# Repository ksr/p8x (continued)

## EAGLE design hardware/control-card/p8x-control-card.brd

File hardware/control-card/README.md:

# Control / Microcode Card

> **Theory of operation:** [p8x-control-card-theory.md](p8x-control-card-theory.md) — deep walkthrough of inputs/outputs, signal flow, and logic.

The brain of the P8X. It generates the clock, handles reset and the front-panel
run controls, holds the instruction register, and — most importantly — runs the
**microcode engine** that drives every other card over the backplane. If a signal
on the bus tells another card what to do (DOE, DLD, PSEL, ALU function, …), it
originated here.

> This README describes the circuit as actually built in
> [`generators/gen_eagle.py`](../../generators/gen_eagle.py) (the canonical
> source). For the architectural overview see
> [p8x-system-design.md §3](../../docs/p8x-system-design.md); for bus pin assignments see
> [p8x-bus-definition.md](../backplane/p8x-bus-definition.md).

## Chip inventory

| Ref | Device | Role |
|-----|--------|------|
| U1 | 74161 | Clock divider (÷2 and ÷4 taps for JP1) |
| U2 | 74HCT14 | Schmitt inverters — reset & switch debounce |
| U3 | 7474 | Dual D flip-flop — run/step synchronizer |
| U4 | 74HCT00 | NAND glue |
| U5 | 74HCT08 | AND glue (clock gating) |
| U6 | 74HCT32 | OR glue |
| U7 | 74377 | Instruction register (8-bit, load-enabled) |
| U8 | 74138 | DLD decoder → generates the IR-load strobe |
| U9 | 74151 | Condition multiplexer (selects 1 of 8 condition sources) |
| U10–U13 | 28C64 | Microcode ROM, 4 × 8 bits = the 32-bit control word |
| U14–U17 | 74374 | Pipeline register (latches the control word on CLK̄) |
| U18 | 74161 | Microcode step counter |
| X1 | 4 MHz osc | Master clock source |

## How it works

### Clock generation
The 4 MHz oscillator (X1) feeds the 74161 divider (U1). Jumper **JP1** (a 2x3
header) selects the raw oscillator or a ÷2/÷4 tap, so you can slow the machine down
for debugging: one shunt on pins 1-2 = 4 MHz, 3-4 = 2 MHz, 5-6 = 1 MHz.
The selected clock is gated (U5/U6) by the run/halt logic and then split into
**CLK** and its inverse **CLK̄** (via U2), both broadcast on the backplane. CLK
clocks the working registers; CLK̄ clocks the pipeline latch a half-cycle earlier
so the control word is already stable when CLK arrives.

### Reset
A pushbutton + RC network feeds two 74HCT14 Schmitt inverters (U2) to produce a
clean, debounced **-RES**. Reset clears the step counter (U18) and the instruction
register (U7), and is broadcast on the backplane so every card returns to a known
state (notably the Register Bank zeroes P0 → execution starts at $0000).

### Front-panel run control
- **RUN/HALT** toggle and a debounced **STEP** pushbutton feed a 7474 (U3)
  synchronizer. Clocking the request through a flip-flop guarantees the machine
  always stops on a **microcycle boundary**, never mid-cycle.
- The microcode **HALT** bit ORs into the same stop logic (U6), so software can
  halt the clock; only the front panel can restart it.

### The microcode engine — the core loop
1. The **instruction register** (U7, a 74377) holds the current opcode. It loads
   from the data bus when the DLD field = 6, decoded by U8 (74138) into the
   `-IRLD` strobe.
2. The microcode ROM address is assembled as **`IR | step<<8 | cond<<12`**:
   - opcode (8 bits) from U7,
   - step number (4 bits) from the U18 step counter,
   - one selected **condition** bit from U9 (74151), chosen by the FCOND field.
3. Four **28C64 EPROMs** (U10–U13) output the 32-bit control word at that address.
4. The 4 × **74374** pipeline latch (U14–U17) registers all 32 bits on CLK̄, so
   glitchy ROM transitions never reach the backplane. The latched outputs *are*
   the bus control signals: DOE0–3, DLD0–3, PSEL0–1, PINC, PDEC, ALUS0–3, ALUM,
   CIN, SH0–1, LDF, FCOND0–2, plus µRESET and HALT.
5. The step counter (U18) increments each cycle. The **µRESET** bit reloads it to
   zero, ending the current instruction and forcing the shared fetch cycle next.

### Condition multiplexer
U9 (74151) selects one of the flag/condition inputs (FC, FZ, FN, FV, hard 0/1, …)
based on the FCOND field, and feeds it into ROM address bit 12. This is how a
single opcode can branch to two different microcode paths (taken vs not-taken)
without any extra sequencing logic — the condition literally selects a different
ROM page.

## Control word layout (32 bits)
See [p8x-system-design.md §3.2](../../docs/p8x-system-design.md) for the full bit map, and
`microcode/genucode.py` `w()` for the authoritative packing. In brief: bits 0–3
DOE, 4–7 DLD, 8–10 PSEL (3-bit: P0–P3 + PT scratch), 11 PINC, 12 PDEC, 13–16 ALU
S0–3, 17 ALU M, 18 CIN, 19–20 SH0/1, 21 LDF, 22–24 FCOND, 25 µRESET, 26 HALT,
27 LDZN, 28 SHCIN, 29 SETC, 30 CLRC, 31 BSEL.

## LEDs
PWR (green), RUN (green), HALT (red) — driven from the run/halt state.

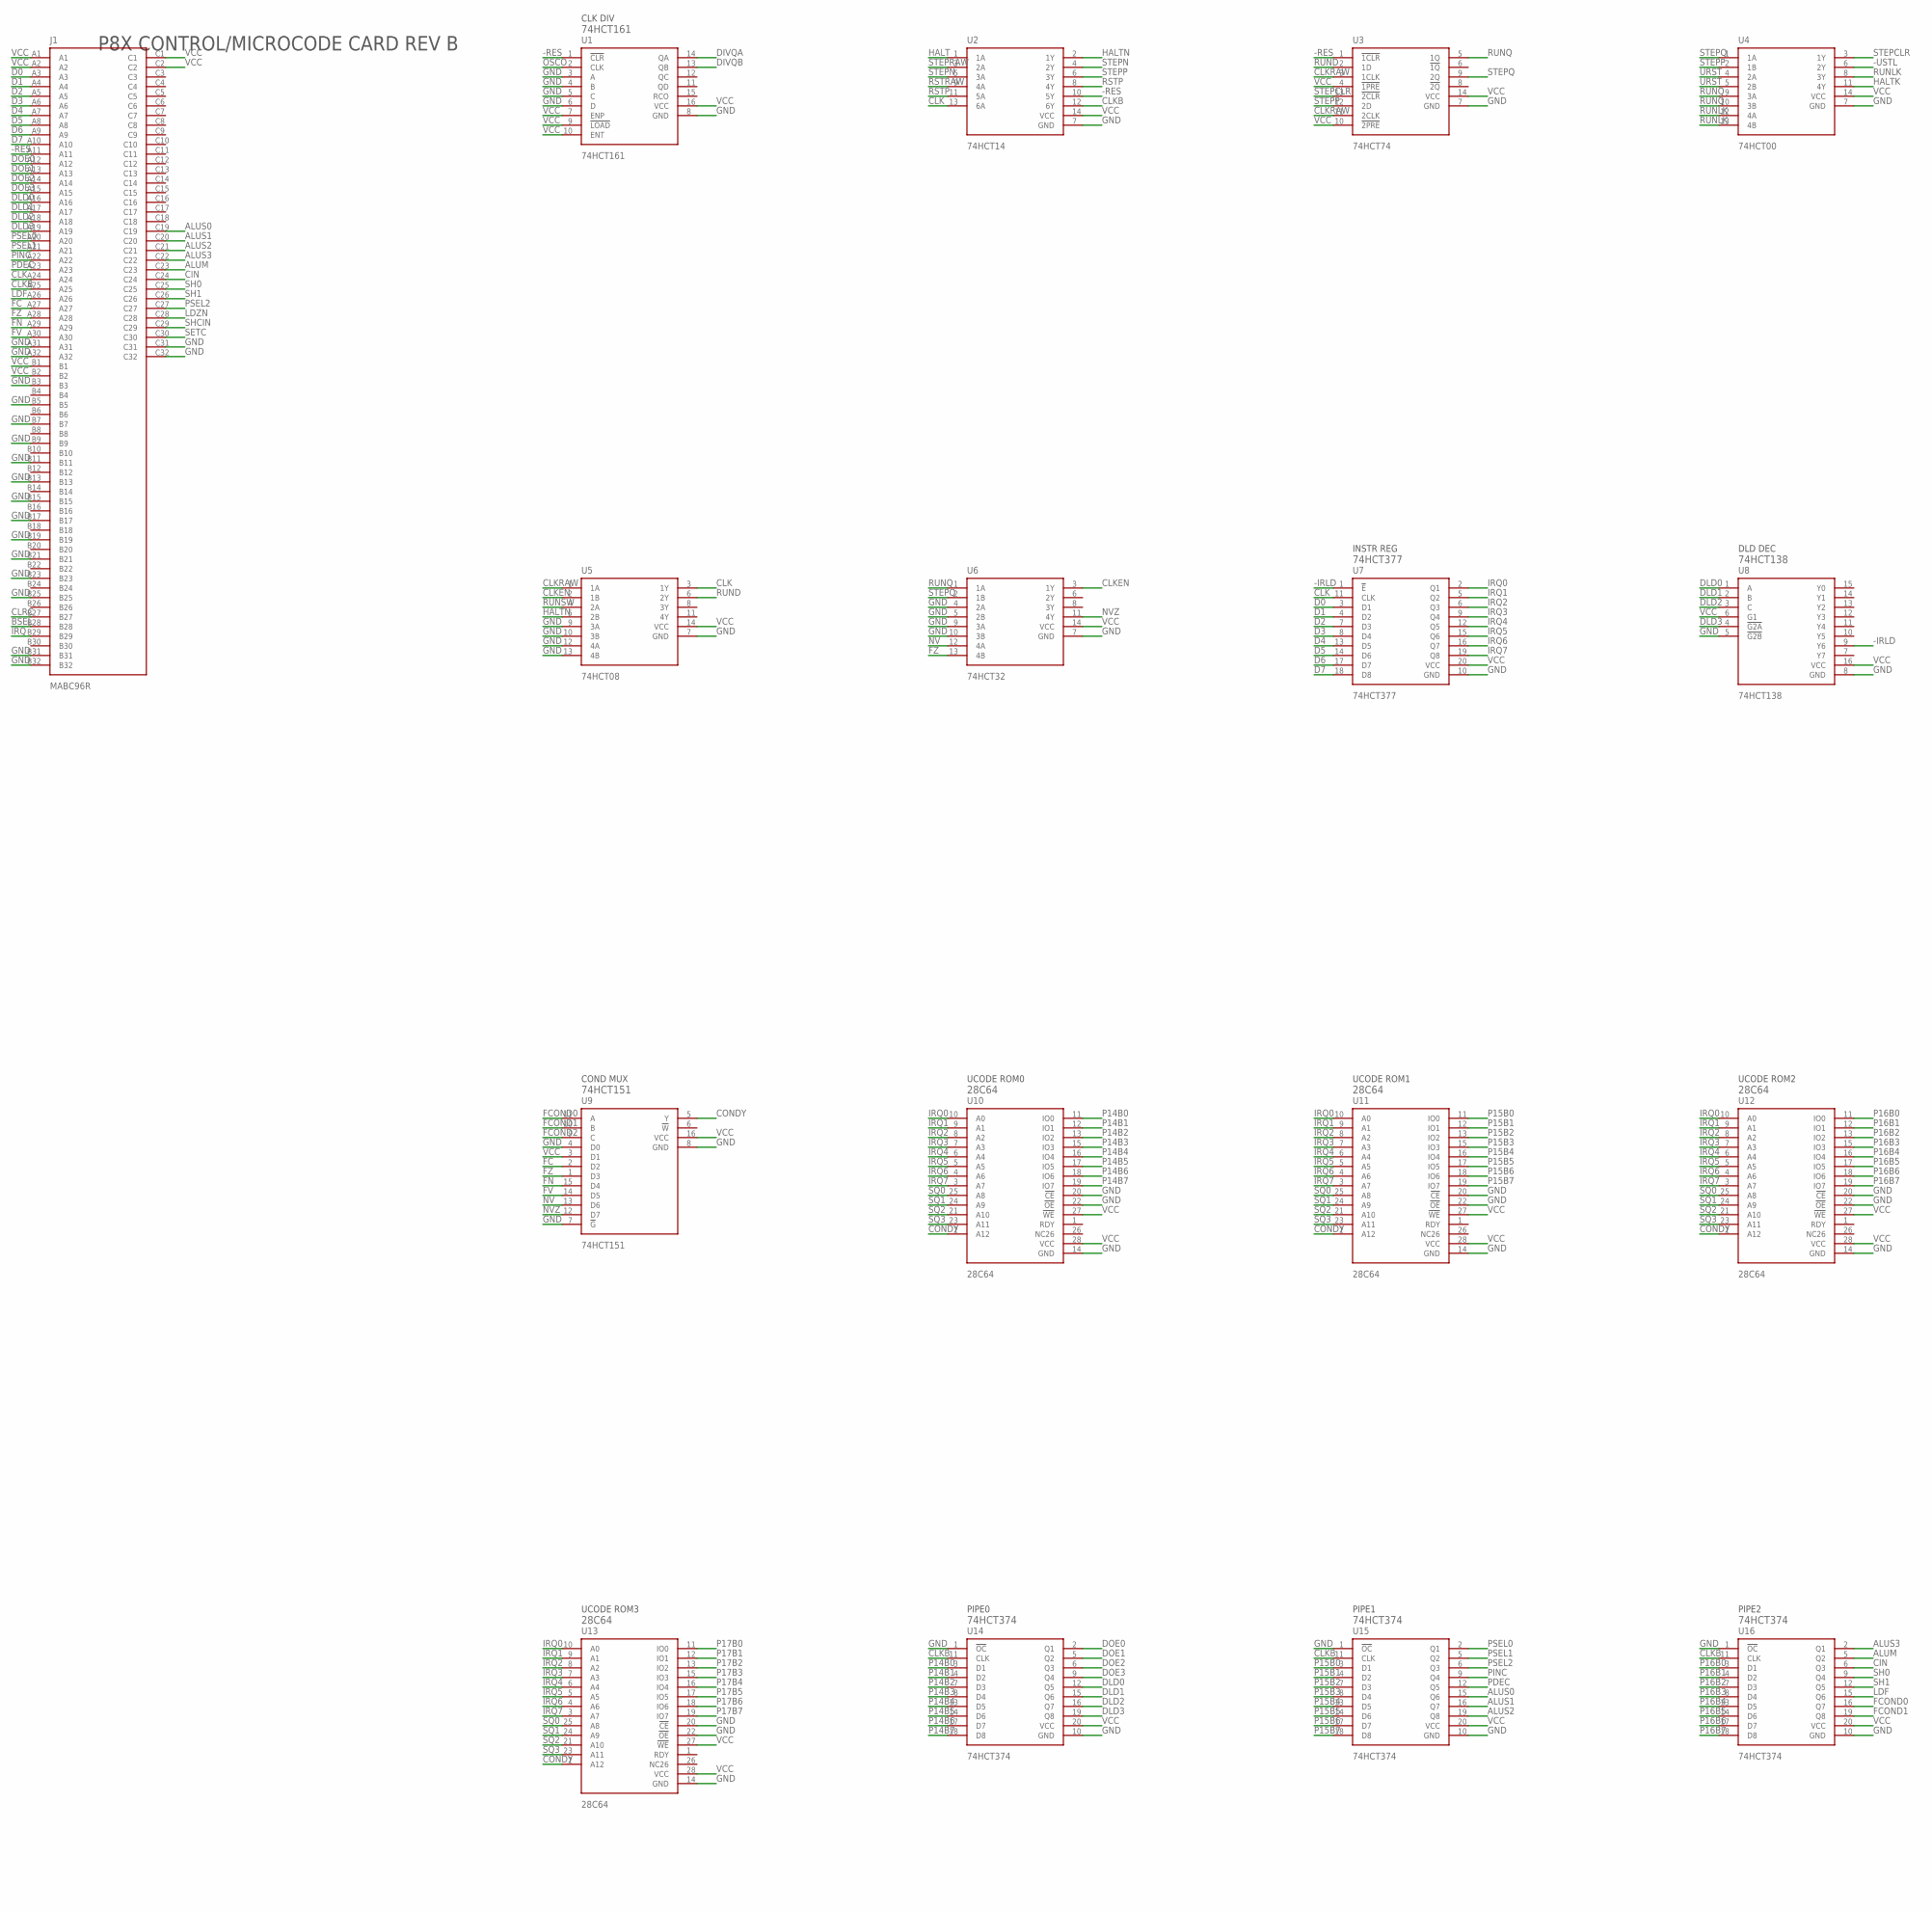
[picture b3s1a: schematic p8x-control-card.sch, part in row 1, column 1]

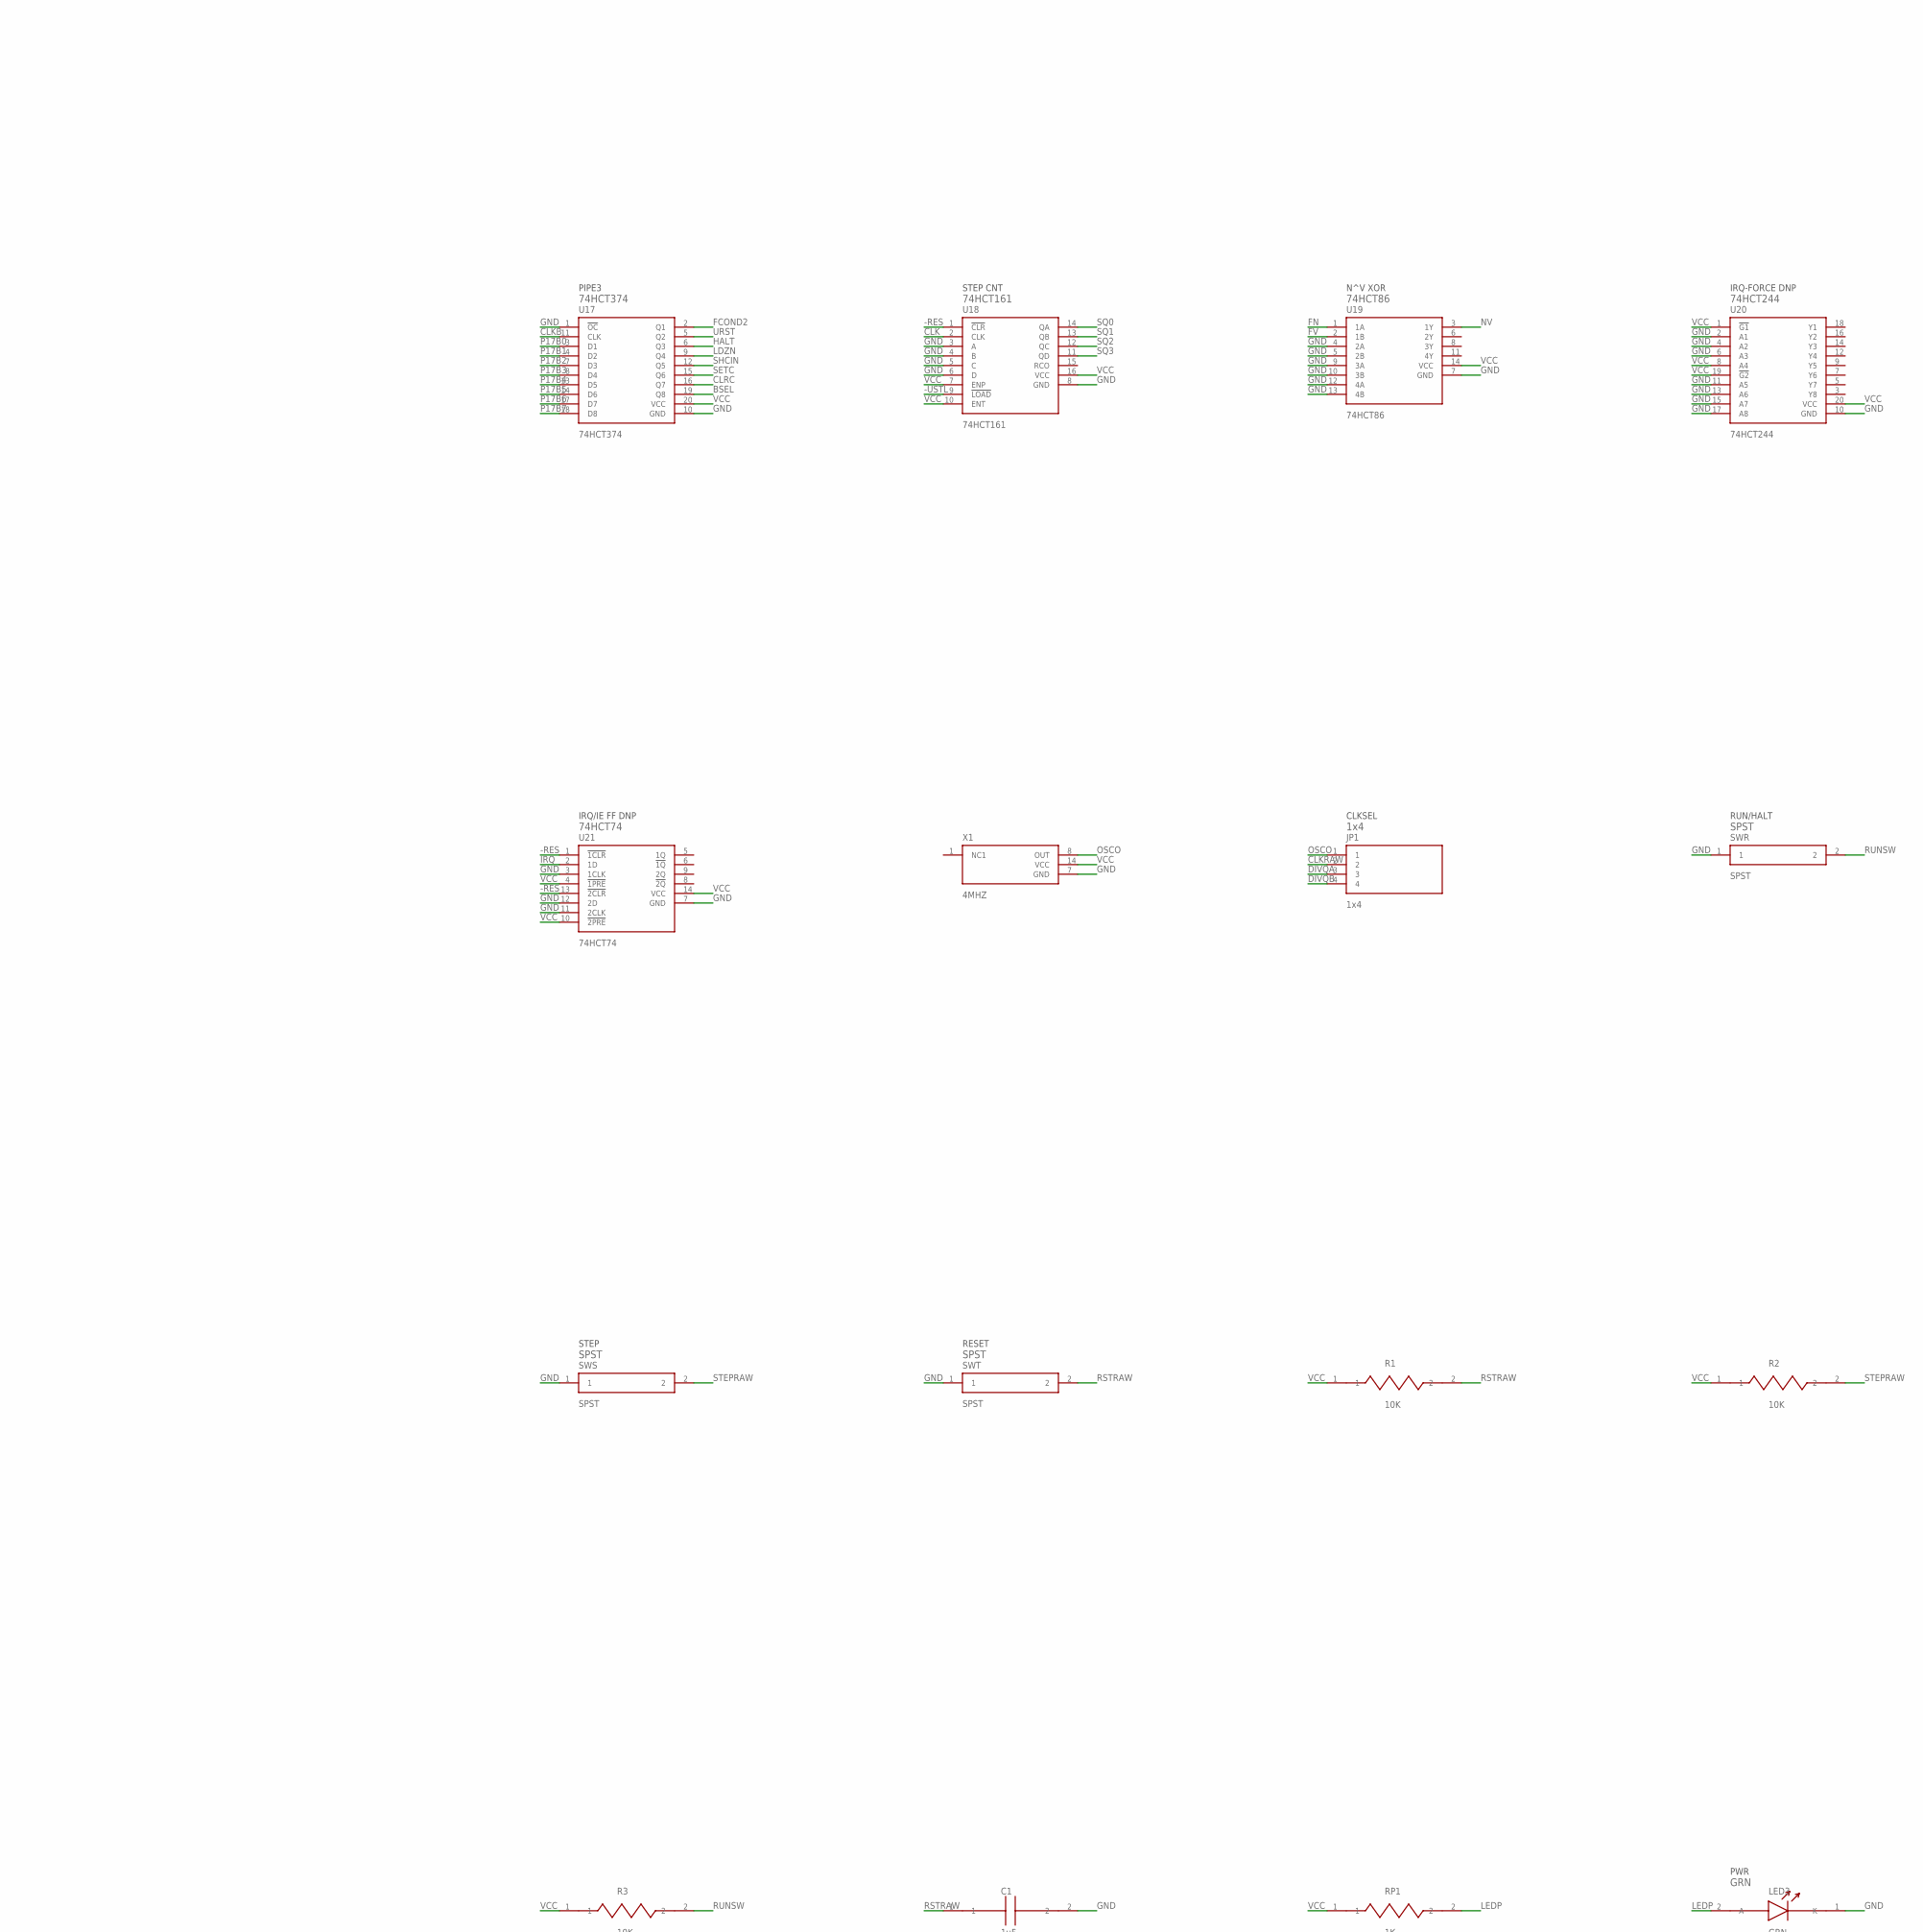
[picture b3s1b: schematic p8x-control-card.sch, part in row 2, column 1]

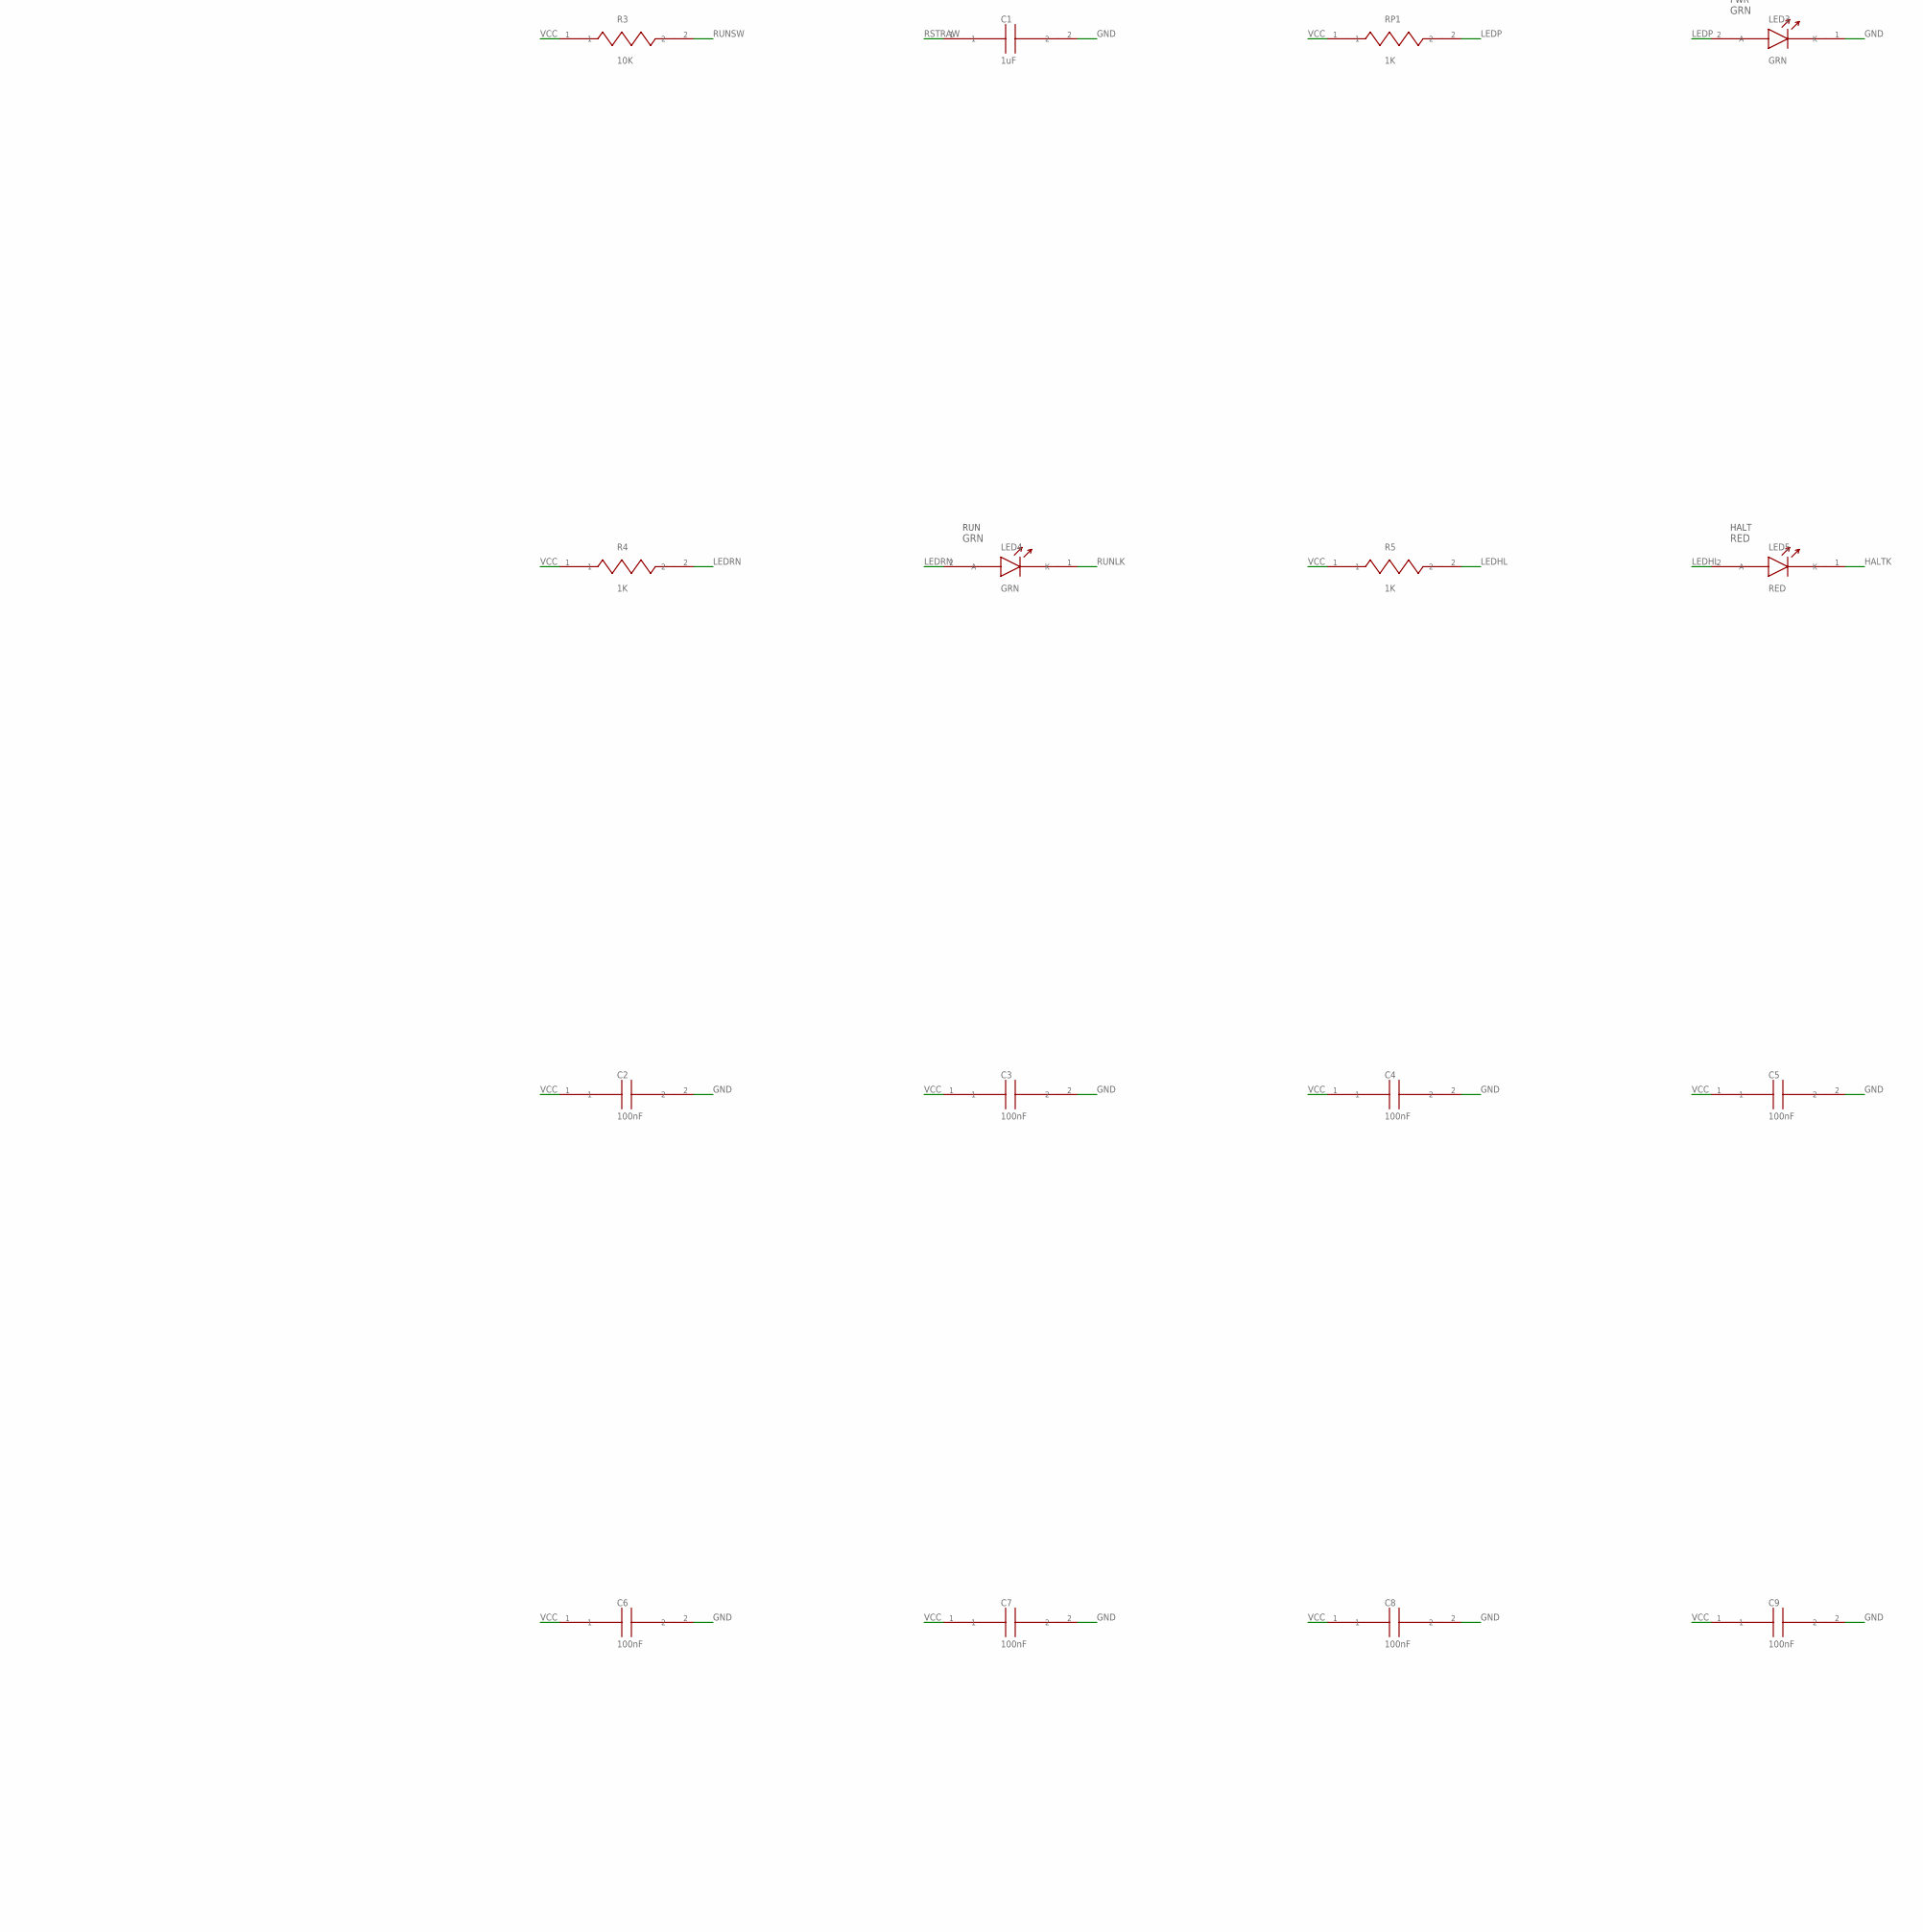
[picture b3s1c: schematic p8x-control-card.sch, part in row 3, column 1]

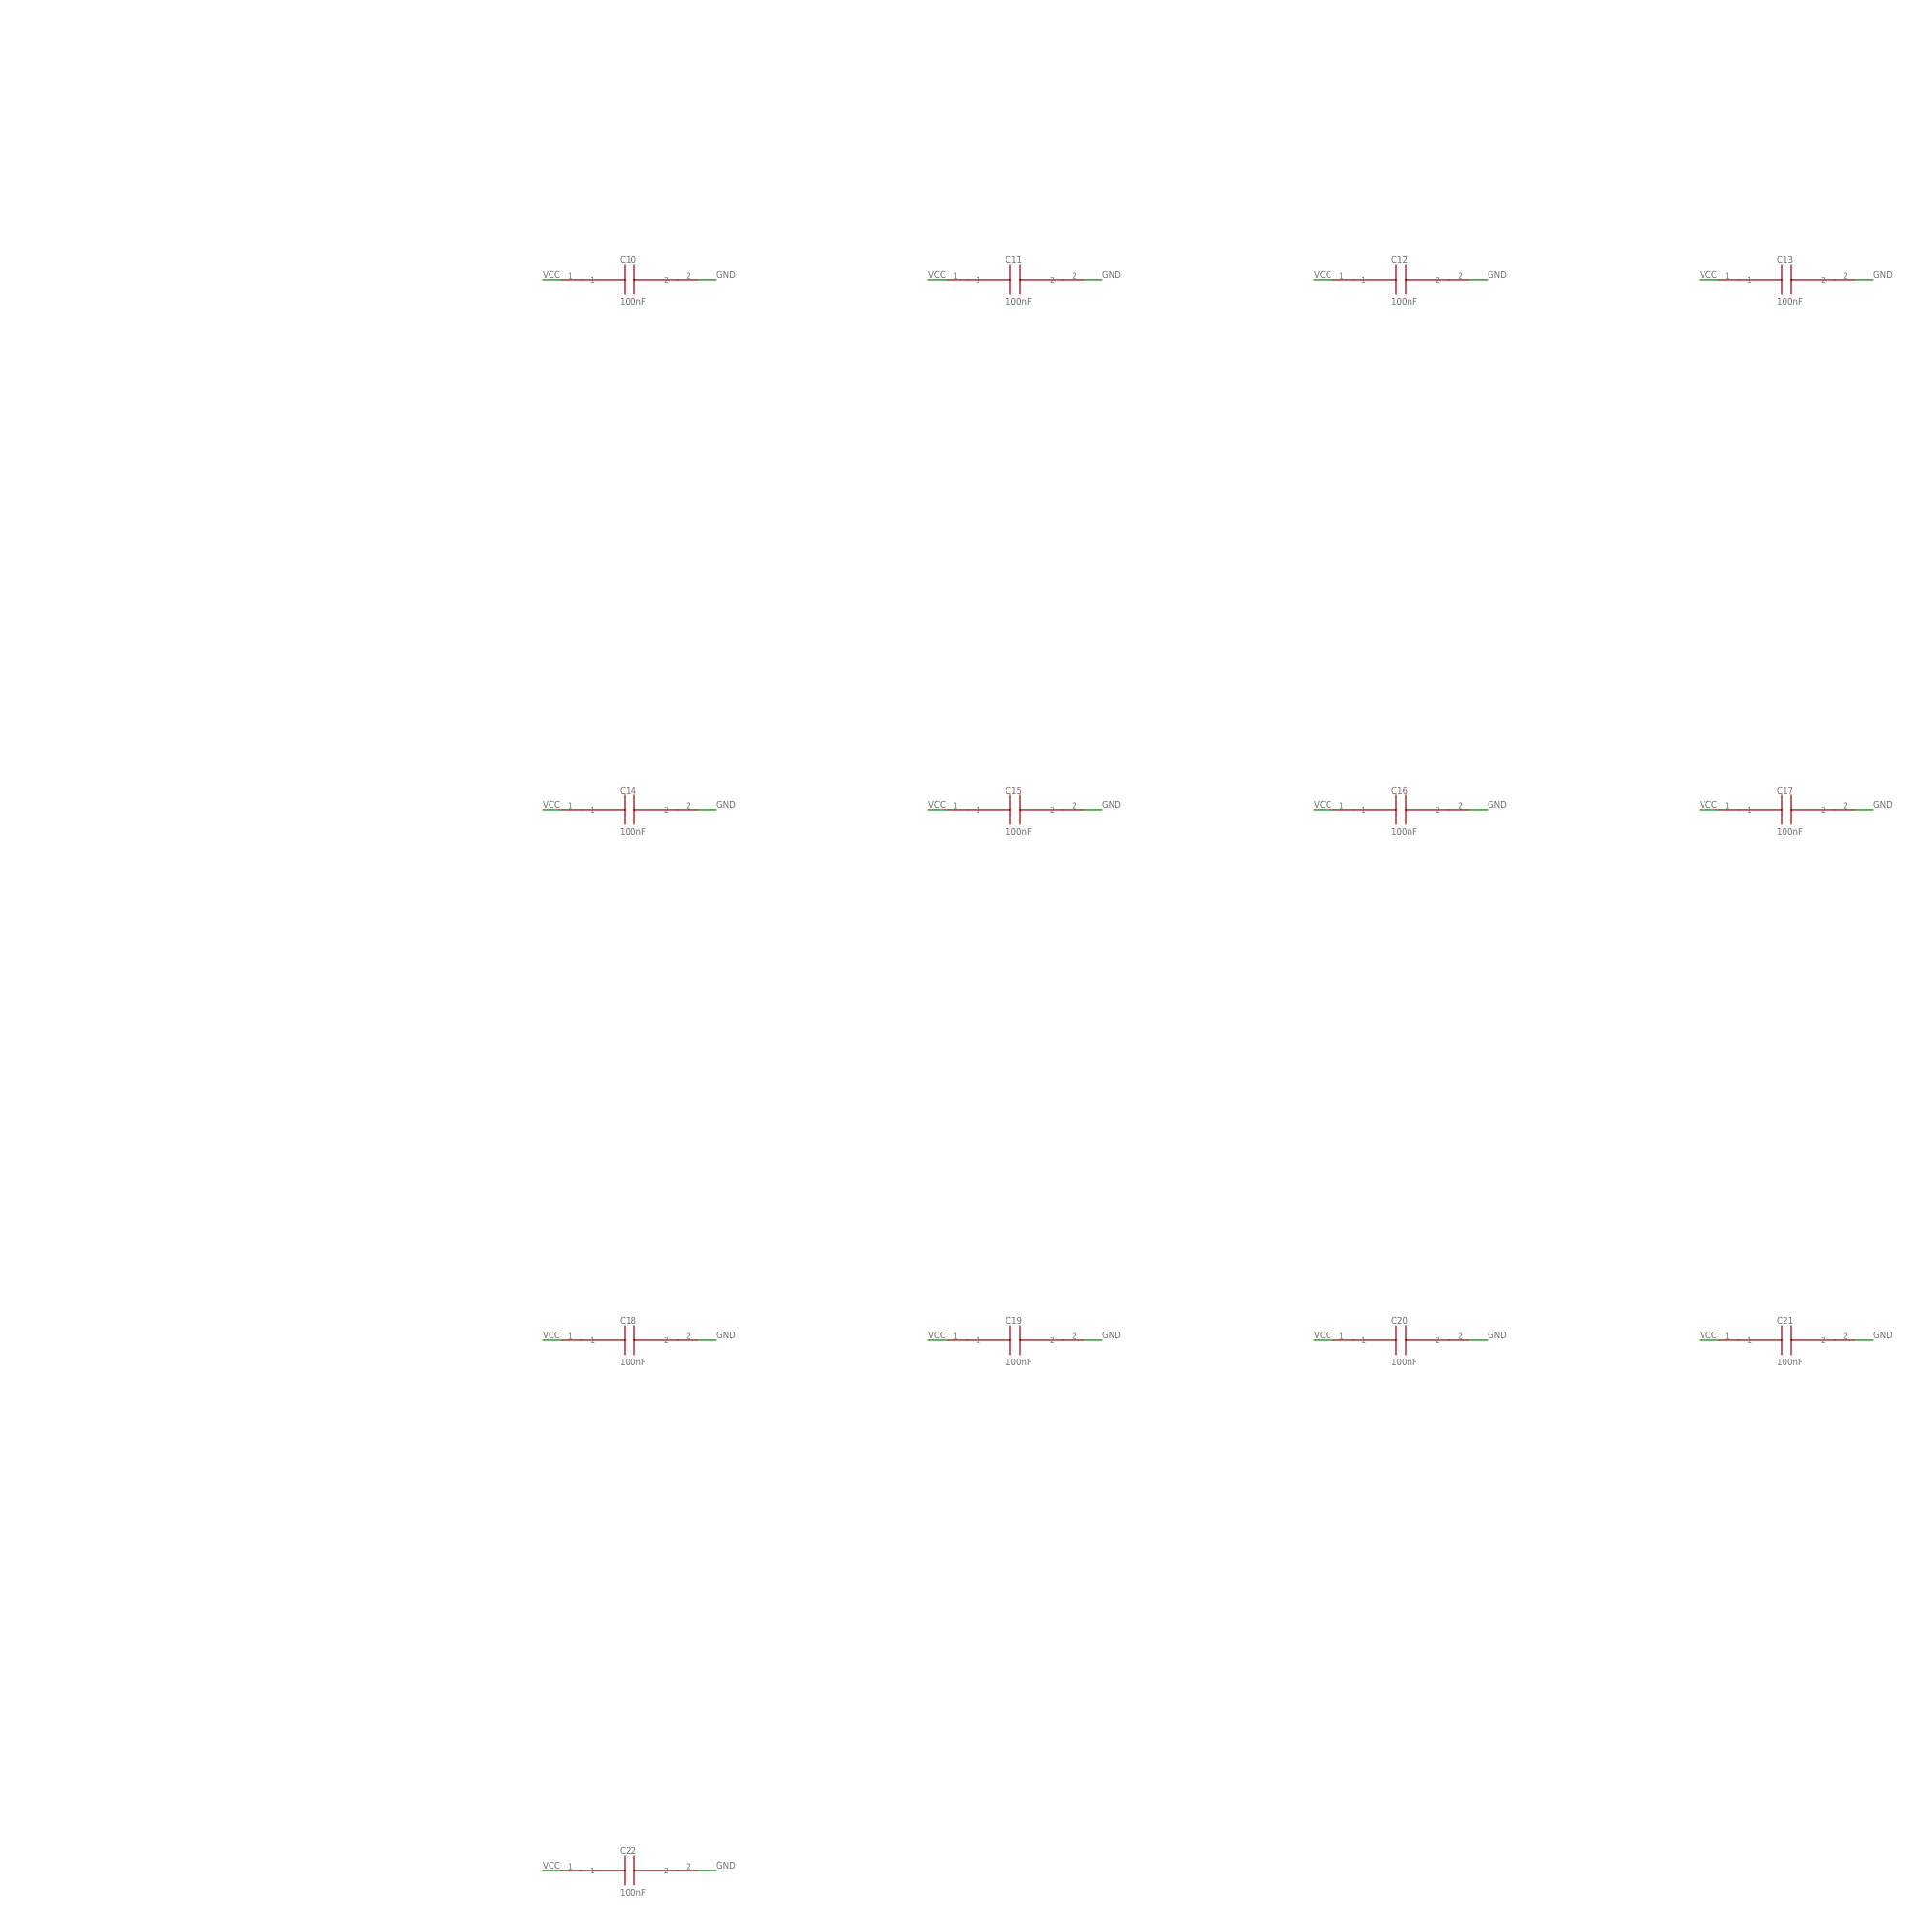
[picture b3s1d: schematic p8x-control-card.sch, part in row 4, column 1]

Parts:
C1: 1uF; C_DISC
C2, C3, C4, C5, C6, C7, C8, C9, C10, C11, C12, C13, C14, C15, C16, C17, C18, C19, C20, C21, C22: 100nF; C_DISC1
J1: MABC96R
JP1: 1x4; HDR4
LED3, LED4: GRN; LED5
LED5: RED; LED5
R1, R2, R3: 10K; R_AXIAL
R4, R5: 1K; R_AXIAL
RP1: 1K; R_AXIAL
SWR: SPST; SW2P
SWS: SPST; SW2P
SWT: SPST; SW2P
U1, U18: 74HCT161; DIP16
U2: 74HCT14; DIP14
U3, U21: 74HCT74; DIP14
U4: 74HCT00; DIP14
U5: 74HCT08; DIP14
U6: 74HCT32; DIP14
U7: 74HCT377; DIP20
U8: 74HCT138; DIP16
U9: 74HCT151; DIP16
U10, U11, U12, U13: 28C64; DIP28W
U14, U15, U16, U17: 74HCT374; DIP20
U19: 74HCT86; DIP14
U20: 74HCT244; DIP20
X1: 4MHZ; OSC4

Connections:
-IRLD: U7.1 (!E), U8.9 (Y6)
-RES: J1.A11, U1.1 (!CLR), U2.10 (5Y), U3.1 (!1CLR), U18.1 (!CLR), U21.1 (!1CLR), U21.13 (!2CLR)
-USTL: U4.6 (2Y), U18.9 (!LOAD)
ALUM: J1.C23, U16.5 (Q2)
ALUS0: J1.C19, U15.15 (Q6)
ALUS1: J1.C20, U15.16 (Q7)
ALUS2: J1.C21, U15.19 (Q8)
ALUS3: J1.C22, U16.2 (Q1)
BSEL: J1.B28, U17.19 (Q8)
CIN: J1.C24, U16.6 (Q3)
CLK: J1.A24, U2.13 (6A), U5.3 (1Y), U7.11 (CLK), U18.2 (CLK)
CLKB: J1.A25, U2.12 (6Y), U14.11 (CLK), U15.11 (CLK), U16.11 (CLK), U17.11 (CLK)
CLKEN: U5.2 (1B), U6.3 (1Y)
CLKRAW: JP1.2, U3.3 (1CLK), U3.11 (2CLK), U5.1 (1A)
CLRC: J1.B27, U17.16 (Q7)
CONDY: U9.5 (Y), U10.2 (A12), U11.2 (A12), U12.2 (A12), U13.2 (A12)
D0: J1.A3, U7.3 (D1)
D1: J1.A4, U7.4 (D2)
D2: J1.A5, U7.7 (D3)
D3: J1.A6, U7.8 (D4)
D4: J1.A7, U7.13 (D5)
D5: J1.A8, U7.14 (D6)
D6: J1.A9, U7.17 (D7)
D7: J1.A10, U7.18 (D8)
DIVQA: JP1.3, U1.14 (QA)
DIVQB: JP1.4, U1.13 (QB)
DLD0: J1.A16, U8.1 (A), U14.12 (Q5)
DLD1: J1.A17, U8.2 (B), U14.15 (Q6)
DLD2: J1.A18, U8.3 (C), U14.16 (Q7)
DLD3: J1.A19, U8.4 (!G2A), U14.19 (Q8)
DOE0: J1.A12, U14.2 (Q1)
DOE1: J1.A13, U14.5 (Q2)
DOE2: J1.A14, U14.6 (Q3)
DOE3: J1.A15, U14.9 (Q4)
FC: J1.A27, U9.2 (D2)
FCOND0: U9.11 (A), U16.16 (Q7)
FCOND1: U9.10 (B), U16.19 (Q8)
FCOND2: U9.9 (C), U17.2 (Q1)
FN: J1.A29, U9.15 (D4), U19.1 (1A)
FV: J1.A30, U9.14 (D5), U19.2 (1B)
FZ: J1.A28, U6.13 (4B), U9.1 (D3)
GND: C1.2, C2.2, C3.2, C4.2, C5.2, C6.2, C7.2, C8.2, C9.2, C10.2, C11.2, C12.2, C13.2, C14.2, C15.2, C16.2, C17.2, C18.2, C19.2, C20.2, C21.2, C22.2, J1.A31, J1.A32, J1.B3, J1.B5, J1.B7, J1.B9, J1.B11, J1.B13, J1.B15, J1.B17, J1.B19, J1.B21, J1.B23, J1.B25, J1.B31, J1.B32, J1.C31, J1.C32, LED3.1 (K), SWR.1, SWS.1, SWT.1, U1.3 (A), U1.4 (B), U1.5 (C), U1.6 (D), U1.8 (GND), U2.7 (GND), U3.7 (GND), U4.7 (GND), U5.7 (GND), U5.9 (3A), U5.10 (3B), U5.12 (4A), U5.13 (4B), U6.4 (2A), U6.5 (2B), U6.7 (GND), U6.9 (3A), U6.10 (3B), U7.10 (GND), U8.5 (!G2B), U8.8 (GND), U9.4 (D0), U9.7 (!G), U9.8 (GND), U10.14 (GND), U10.20 (!CE), U10.22 (!OE), U11.14 (GND), U11.20 (!CE), U11.22 (!OE), U12.14 (GND), U12.20 (!CE), U12.22 (!OE), U13.14 (GND), U13.20 (!CE), U13.22 (!OE), U14.1 (!OC), U14.10 (GND), U15.1 (!OC), U15.10 (GND), U16.1 (!OC), U16.10 (GND), U17.1 (!OC), U17.10 (GND), U18.3 (A), U18.4 (B), U18.5 (C), U18.6 (D), U18.8 (GND), U19.4 (2A), U19.5 (2B), U19.7 (GND), U19.9 (3A), U19.10 (3B), U19.12 (4A), U19.13 (4B), U20.2 (A1), U20.4 (A2), U20.6 (A3), U20.10 (GND), U20.11 (A5), U20.13 (A6), U20.15 (A7), U20.17 (A8), U21.3 (1CLK), U21.7 (GND), U21.11 (2CLK), U21.12 (2D), X1.7 (GND)
HALT: U2.1 (1A), U17.6 (Q3)
HALTK: LED5.1 (K), U4.11 (4Y)
HALTN: U2.2 (1Y), U5.5 (2B)
IRQ: J1.B29, U21.2 (1D)
IRQ0: U7.2 (Q1), U10.10 (A0), U11.10 (A0), U12.10 (A0), U13.10 (A0)
IRQ1: U7.5 (Q2), U10.9 (A1), U11.9 (A1), U12.9 (A1), U13.9 (A1)
IRQ2: U7.6 (Q3), U10.8 (A2), U11.8 (A2), U12.8 (A2), U13.8 (A2)
IRQ3: U7.9 (Q4), U10.7 (A3), U11.7 (A3), U12.7 (A3), U13.7 (A3)
IRQ4: U7.12 (Q5), U10.6 (A4), U11.6 (A4), U12.6 (A4), U13.6 (A4)
IRQ5: U7.15 (Q6), U10.5 (A5), U11.5 (A5), U12.5 (A5), U13.5 (A5)
IRQ6: U7.16 (Q7), U10.4 (A6), U11.4 (A6), U12.4 (A6), U13.4 (A6)
IRQ7: U7.19 (Q8), U10.3 (A7), U11.3 (A7), U12.3 (A7), U13.3 (A7)
LDF: J1.A26, U16.15 (Q6)
LDZN: J1.C28, U17.9 (Q4)
LEDHL: LED5.2 (A), R5.2
LEDP: LED3.2 (A), RP1.2
LEDRN: LED4.2 (A), R4.2
NV: U6.12 (4A), U9.13 (D6), U19.3 (1Y)
NVZ: U6.11 (4Y), U9.12 (D7)
OSCO: JP1.1, U1.2 (CLK), X1.8 (OUT)
P14B0: U10.11 (IO0), U14.3 (D1)
P14B1: U10.12 (IO1), U14.4 (D2)
P14B2: U10.13 (IO2), U14.7 (D3)
P14B3: U10.15 (IO3), U14.8 (D4)
P14B4: U10.16 (IO4), U14.13 (D5)
P14B5: U10.17 (IO5), U14.14 (D6)
P14B6: U10.18 (IO6), U14.17 (D7)
P14B7: U10.19 (IO7), U14.18 (D8)
P15B0: U11.11 (IO0), U15.3 (D1)
P15B1: U11.12 (IO1), U15.4 (D2)
P15B2: U11.13 (IO2), U15.7 (D3)
P15B3: U11.15 (IO3), U15.8 (D4)
P15B4: U11.16 (IO4), U15.13 (D5)
P15B5: U11.17 (IO5), U15.14 (D6)
P15B6: U11.18 (IO6), U15.17 (D7)
P15B7: U11.19 (IO7), U15.18 (D8)
P16B0: U12.11 (IO0), U16.3 (D1)
P16B1: U12.12 (IO1), U16.4 (D2)
P16B2: U12.13 (IO2), U16.7 (D3)
P16B3: U12.15 (IO3), U16.8 (D4)
P16B4: U12.16 (IO4), U16.13 (D5)
P16B5: U12.17 (IO5), U16.14 (D6)
P16B6: U12.18 (IO6), U16.17 (D7)
P16B7: U12.19 (IO7), U16.18 (D8)
P17B0: U13.11 (IO0), U17.3 (D1)
P17B1: U13.12 (IO1), U17.4 (D2)
P17B2: U13.13 (IO2), U17.7 (D3)
P17B3: U13.15 (IO3), U17.8 (D4)
P17B4: U13.16 (IO4), U17.13 (D5)
P17B5: U13.17 (IO5), U17.14 (D6)
P17B6: U13.18 (IO6), U17.17 (D7)
P17B7: U13.19 (IO7), U17.18 (D8)
PDEC: J1.A23, U15.12 (Q5)
PINC: J1.A22, U15.9 (Q4)
PSEL0: J1.A20, U15.2 (Q1)
PSEL1: J1.A21, U15.5 (Q2)
PSEL2: J1.C27, U15.6 (Q3)
RSTP: U2.8 (4Y), U2.11 (5A)
RSTRAW: C1.1, R1.2, SWT.2, U2.9 (4A)
RUND: U3.2 (1D), U5.6 (2Y)
RUNLK: LED4.1 (K), U4.8 (3Y), U4.12 (4A), U4.13 (4B)
RUNQ: U3.5 (1Q), U4.9 (3A), U4.10 (3B), U6.1 (1A)
RUNSW: R3.2, SWR.2, U5.4 (2A)
SETC: J1.C30, U17.15 (Q6)
SH0: J1.C25, U16.9 (Q4)
SH1: J1.C26, U16.12 (Q5)
SHCIN: J1.C29, U17.12 (Q5)
SQ0: U10.25 (A8), U11.25 (A8), U12.25 (A8), U13.25 (A8), U18.14 (QA)
SQ1: U10.24 (A9), U11.24 (A9), U12.24 (A9), U13.24 (A9), U18.13 (QB)
SQ2: U10.21 (A10), U11.21 (A10), U12.21 (A10), U13.21 (A10), U18.12 (QC)
SQ3: U10.23 (A11), U11.23 (A11), U12.23 (A11), U13.23 (A11), U18.11 (QD)
STEPCLR: U3.13 (!2CLR), U4.3 (1Y)
STEPN: U2.4 (2Y), U2.5 (3A)
STEPP: U2.6 (3Y), U3.12 (2D), U4.2 (1B)
STEPQ: U3.9 (2Q), U4.1 (1A), U6.2 (1B)
STEPRAW: R2.2, SWS.2, U2.3 (2A)
URST: U4.4 (2A), U4.5 (2B), U17.5 (Q2)
VCC: C2.1, C3.1, C4.1, C5.1, C6.1, C7.1, C8.1, C9.1, C10.1, C11.1, C12.1, C13.1, C14.1, C15.1, C16.1, C17.1, C18.1, C19.1, C20.1, C21.1, C22.1, J1.A1, J1.A2, J1.B1, J1.B2, J1.C1, J1.C2, R1.1, R2.1, R3.1, R4.1, R5.1, RP1.1, U1.7 (ENP), U1.9 (!LOAD), U1.10 (ENT), U1.16 (VCC), U2.14 (VCC), U3.4 (!1PRE), U3.10 (!2PRE), U3.14 (VCC), U4.14 (VCC), U5.14 (VCC), U6.14 (VCC), U7.20 (VCC), U8.6 (G1), U8.16 (VCC), U9.3 (D1), U9.16 (VCC), U10.27 (!WE), U10.28 (VCC), U11.27 (!WE), U11.28 (VCC), U12.27 (!WE), U12.28 (VCC), U13.27 (!WE), U13.28 (VCC), U14.20 (VCC), U15.20 (VCC), U16.20 (VCC), U17.20 (VCC), U18.7 (ENP), U18.10 (ENT), U18.16 (VCC), U19.14 (VCC), U20.1 (!G1), U20.8 (A4), U20.19 (!G2), U20.20 (VCC), U21.4 (!1PRE), U21.10 (!2PRE), U21.14 (VCC), X1.14 (VCC)

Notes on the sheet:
P8X CONTROL/MICROCODE CARD REV B
N^V XOR
74HCT86
CLK DIV
74HCT161
INSTR REG
74HCT377
DLD DEC
74HCT138
COND MUX
74HCT151
UCODE ROM0
28C64
UCODE ROM1
UCODE ROM2
UCODE ROM3
PIPE0
74HCT374
PIPE1
PIPE2
PIPE3
STEP CNT
IRQ-FORCE DNP
74HCT244
IRQ/IE FF DNP
74HCT74
CLKSEL
1x4
RUN/HALT
SPST
STEP
RESET
PWR
GRN
RUN
HALT
RED

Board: 4 copper layers, 58 parts (0 on the bottom side), 120 nets, no tracks yet.
